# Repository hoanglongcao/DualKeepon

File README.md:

# DualKeepon
A portable system with My Keepon robots to study linguistic and para-linguistic features of speech

This project is a collaboration between:
>Robotics and Multibody Mechanics Research Group (Vrije Universiteit Brussel)

>Human-Robot Interaction Lab (University of Southern Denmark).

Contact:
> Hoang-Long Cao: hoancao (at) vub (dot) ac (dot) be

> Lars Christian Jensen: larscj (at) sdu (dot) dk

## Publications

1. Cao, H.L., Jensen, L.C., Nghiem, X.N., Vu, H., De Beir, A., Esteban, P.G., Van de Perre, G., Lefeber, D. and Vanderborght, B., 2019. DualKeepon: a human–robot interaction testbed to study linguistic features of speech. Intelligent Service Robotics, 12(1), pp.45-54.

2. Cao, H.L., Van de Perre, G., Simut, R., Pop, C., Peca, A., Lefeber, D. and Vanderborght, B., 2014, August. Enhancing My Keepon robot: A simple and low-cost solution for robot platform in Human-Robot Interaction studies. In The 23rd IEEE International Symposium on Robot and Human Interactive Communication (pp. 555-560). IEEE.

## Hacking MyKeepon

A tutorial of hacking MyKeepon robot can  be found in our website: http://probo.vub.ac.be/HackingKeepon. For this DualKeepon project, no shield for Arduino is needed.

This work was presented at the 2013 International Summer School on Social HRI and RO-MAN 2014.

Atelier 3: Hacking Keepon – Bram Vanderborght, Cao Hoang Long, Greet Van de Perre (Vrije Universiteit Brussel, Belgium) and James Kennedy and Tony Belpaeme (Plymouth University, UK)
http://www.tech.plymouth.ac.uk/SoccE/ALIZ-E/summerschool/programme2.html

H.-L. Cao, G. Van de Perre, R. Simut, C. Pop, A. Peca, D. Lefeber, and B. Vanderborght, "Enhancing my keepon robot: A simple and low-cost solution for robot platform in human-robot interaction studies," in Proceedings of the 23rd IEEE International Symposium on Robot and Human Interactive Communication, Edinburgh, UK, August 2014, pp. 555-560. 
http://ieeexplore.ieee.org/xpl/articleDetails.jsp?arnumber=6926311

## Hardware

The schematic and PCB layout can be downloaded here: https://github.com/hoanglongcao/DualKeepon/tree/master/PCB

Bill of material for our PCB:

> Arduino Nao x 2: https://www.arduino.cc/en/Main/ArduinoBoardNano

> 

> PAM8403 amplifier board: https://www.amazon.co.uk/Super-PAM8403-Digital-Amplifier-2-5-5V-Black/dp/B00EZI0RGA

> 

> SparkFun TRRS 3.5mm Jack Breakout: https://www.sparkfun.com/products/11570

> 

Harware connection

>Upload the Arduino firmware (new and stable). Arduino Nano with ATmega328P. Baud rate 9600.

>Connect 2 Arduinos to 2 USB ports of PC.

>Connect to the stereo output of PC.

>Connect to LEFT Keepon and RIGHT Keepon. The connector has 6 contact points: (V0,CL,DA,GND) as in the previous Hacking Keepon project, and (S+ and S-) which are the connection to Keepon’s speaker. The (X) pin is unused.

How to connect to Keepon’s speaker: Pull out the speaker connection and connect it with 2 wires to (S+ and S-).

##How to use the software
Visual Studio 2013 is used. New versions should be able to run the software. The software source code can be downloaded here: https://github.com/hoanglongcao/DualKeepon/tree/master/Software-VS2013

After running the software, 2 windows appear to connect with 2 Keepons by selecting the corresponding COM Ports. Make sure that you connect the ViKeepon LEFT to the LEFT Keepon and the ViKeepon RIGHT to the right one. You can test if you connect correctly by clicking Jump or Bend button.

>In case you make a wrong connection, click close port and choose another port. Then click Open port again.
Input UserName and Gender then RUN EXPERIMENT. These data is used to create a text file with user data and his/her answers later in the experiment.

An experiment window will appear in fullscreen mode.

Click START to begin the experiment when user is ready.

The software then loads all questions in the database. See next section How to create the database.

Click NEXT to move to the next question.

After the experiment finished, Keepon says Thank you and user can QUIT or View Log to review their answers. This log is also saved in a text file under “users” folder.

>If the same user runs again the experiment, the log file will be continued. Each experiment log is saved together with the time.

## Create the database

The database is organized as the following figure.  If you are using VS to run the software, the database is stored under bin/Debug/_data/

question_xx folder is used to store the context of question number xx.

>Pictures of the left and right images must be name 1 and 2.

>question.txt: your text for the question.

>	_audio folder: store the audio files for the question. The number of files is unlimited. You need to follow the format : <1....n>_<Paul/Paula>. You should create these sound files with only left (for Paul) or right channel (for Paula).

user folder is used to store the log file (username, gender, answers)

sound files for great choice and thank you

Picture files 1 and 2 for the screen of saying goodbye.

File extensions:
>Pictures: jpg, jpef, png, gif, bmp

>Sounds: mp3, wav, wma, w4a, ogg

>If you want to add more extensions, edit the source code.

## Important notes
If you want to replace the files, keep the same names.

Feel free to modify the source code.

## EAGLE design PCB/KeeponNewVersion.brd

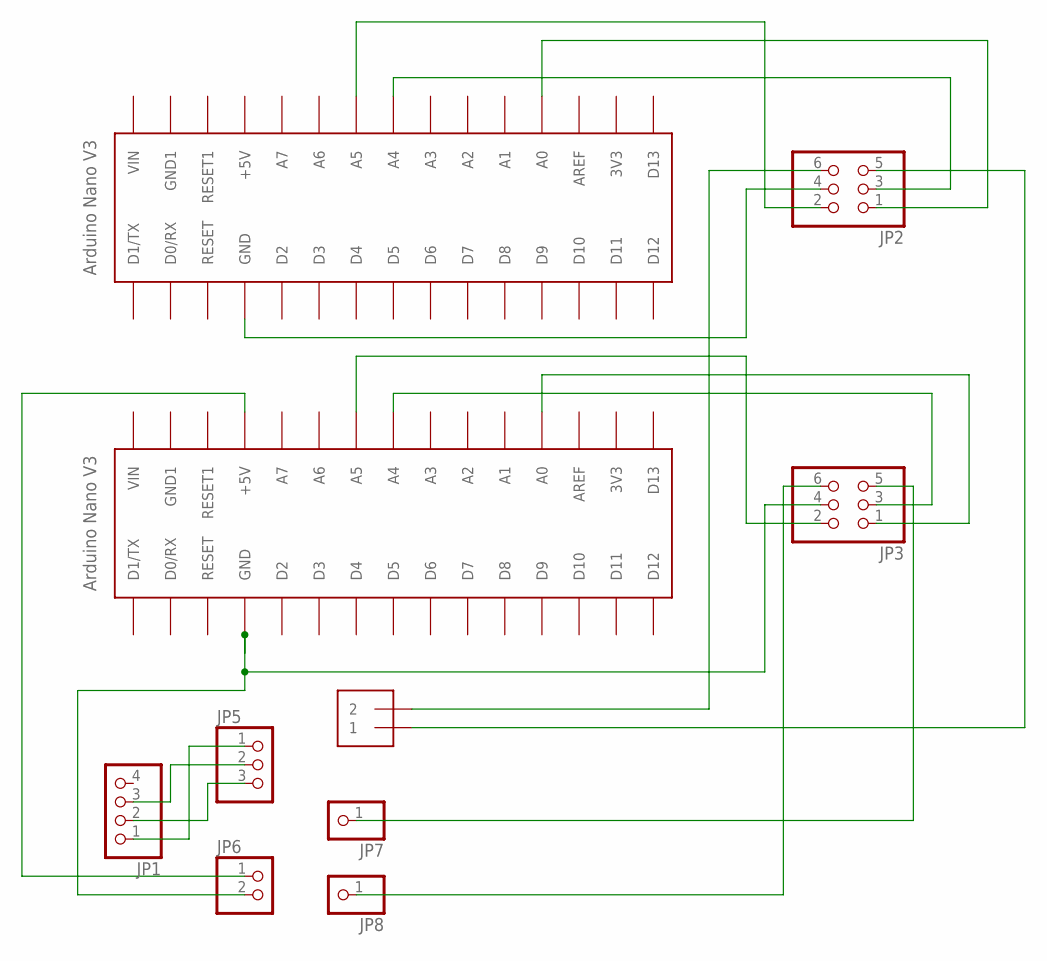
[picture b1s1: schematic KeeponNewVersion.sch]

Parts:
J1: 1X2-3.5MM
JP1: PINHD-1X4; 1X04
JP2, JP3: PINHD-2X3; 2X03
JP5: PINHD-1X3; 1X03
JP6: PINHD-1X2; 1X02
JP7, JP8: PINHD-1X1; 1X01
U$2, U$3: ARDUINONANO; PDIP-32

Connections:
GND: JP2.4, JP3.4, JP6.2, U$2.GND, U$3.GND
unnamed: JP2.1, U$3.A7 (A0)
unnamed: JP2.2, U$3.A2 (A5)
unnamed: JP2.3, U$3.A3 (A4)
unnamed: JP3.1, U$2.A7 (A0)
unnamed: JP3.3, U$2.A3 (A4)
unnamed: JP3.2, U$2.A2 (A5)
unnamed: J1.1, JP2.5
unnamed: J1.2, JP2.6
unnamed: JP3.5, JP7.1
unnamed: JP3.6, JP8.1
unnamed: JP1.1, JP5.1
unnamed: JP1.2, JP5.3
unnamed: JP1.3, JP5.2
unnamed: JP6.1, U$2.+5V

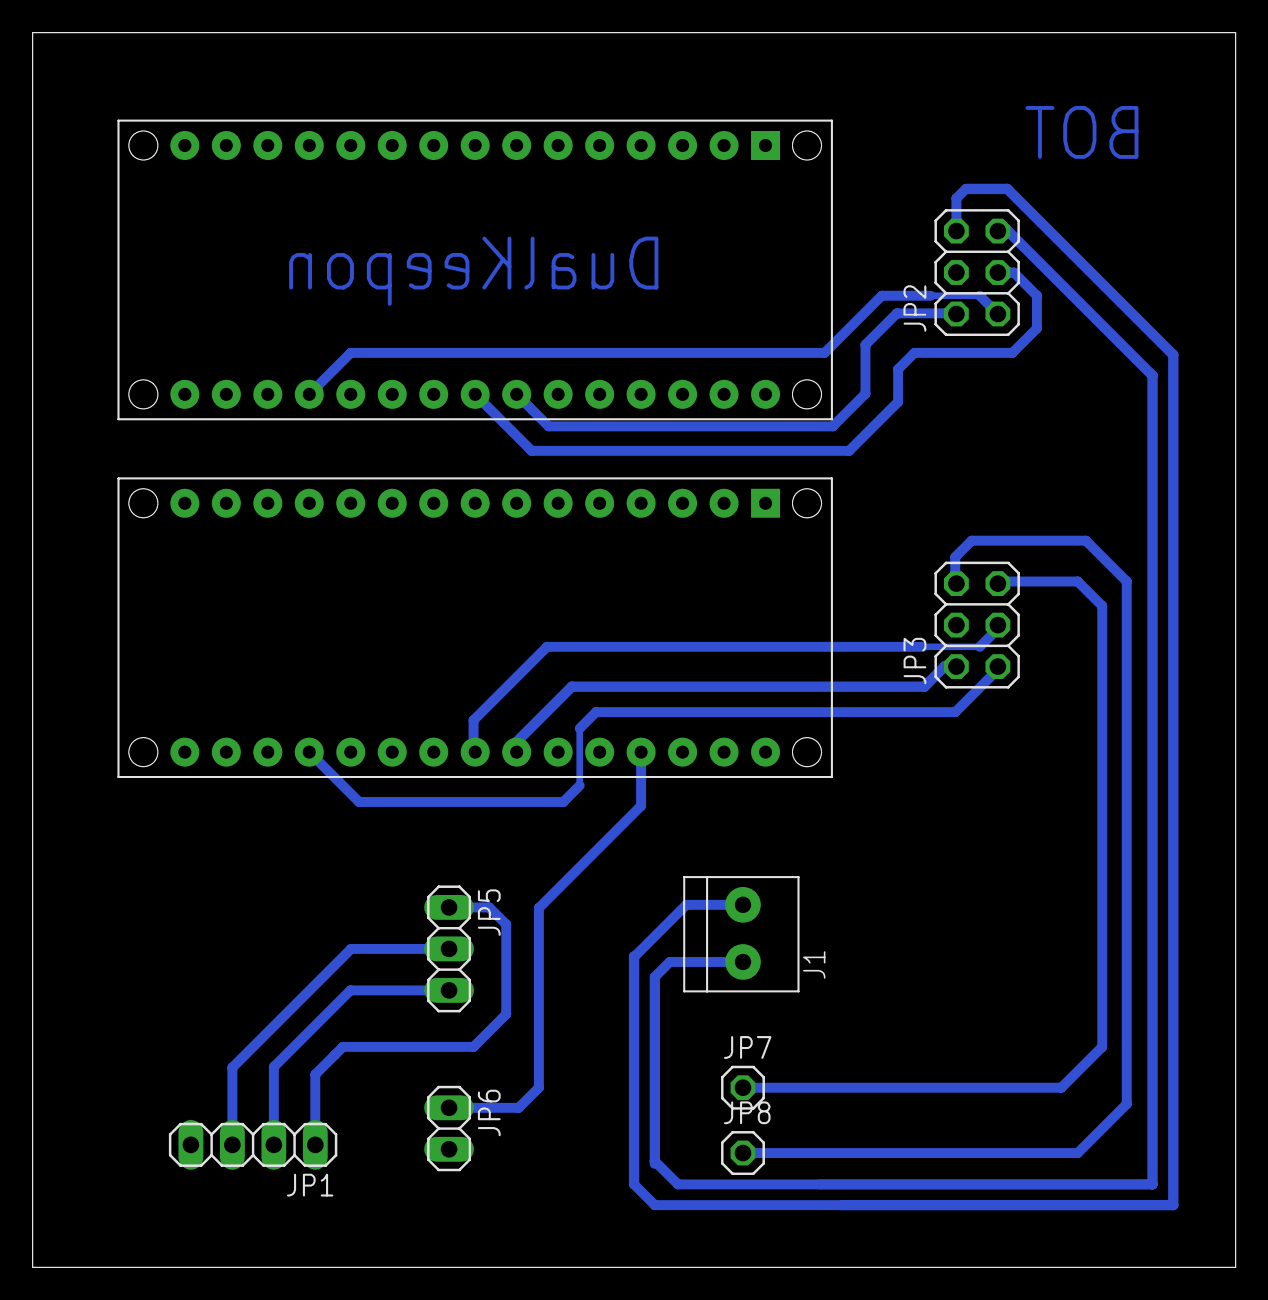
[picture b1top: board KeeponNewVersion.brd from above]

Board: 2 copper layers, 73.7 x 75.6 mm, 10 parts (0 on the bottom side), 15 nets.

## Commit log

2016-09-08 Revert "Add files via upload"
    This reverts commit 13b1197608c5e8212dc3978681f4400c38eee2fe.
2016-09-08 Add the software
2018-09-07 Rename folder
